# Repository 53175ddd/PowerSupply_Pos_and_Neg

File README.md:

# 正負出力電源装置

## 概要

DC 9 ~ 12V を入力すると，正負出力に変換する電源回路です  
実装する定電圧レギュレータにより出力電圧が異なります

| 正側レギュレータ（U2）の種類 | 出力電圧 | 負側レギュレータ（U3）の種類 | 出力電圧 |
|:----:|----:|:----:|----:|
| NJM7812 | 12V | NJM7912 | -12V |
| NJM7809 | 9V | NJM7909 | -9V |
| NJM7805 | 5V | NJM7905 | -5V |

## 部品表

| アノテーション | 部品定数等 | リンク |
|:----|:----|:----|
| C1 - C4 | 1uF | <https://akizukidenshi.com/catalog/g/gP-08150/> |
| C5 | 470pF | <https://akizukidenshi.com/catalog/g/gP-08130/> |
| C6 - C9 | 0.1uF | <https://akizukidenshi.com/catalog/g/gP-10147/> |
| D1 - D3 | 1N4148 | <https://akizukidenshi.com/catalog/g/gI-00941/> |
| D4 | 1JU41 | <https://akizukidenshi.com/catalog/g/gI-12820/> |
| J1 | 2.1mm DC ジャック | <https://akizukidenshi.com/catalog/g/gC-06568/> |
| J2 | 3P ターミナルブロック | <https://akizukidenshi.com/catalog/g/gP-01307/> |
| L1 | 220uH | <https://akizukidenshi.com/catalog/g/gP-13381/> |
| Q1 | TK20A60U | <https://akizukidenshi.com/catalog/g/gI-08419/> |
| Q2 | 2SA1015 | <https://akizukidenshi.com/catalog/g/gI-02612/> |
| R1 | 330Ω | <https://akizukidenshi.com/catalog/g/gR-25331/> |
| R2 | 12kΩ | <https://akizukidenshi.com/catalog/g/gR-25123/> |
| R3 | 1kΩ | <https://akizukidenshi.com/catalog/g/gR-16102/> |
| U1 | NJM2374 | <https://akizukidenshi.com/catalog/g/gI-12901/> |
| U2 | NJM7812 等 | <https://akizukidenshi.com/catalog/g/gI-00163/> |
| U3 | NJM7912 等 | <https://akizukidenshi.com/catalog/g/gI-17482/> |

## 回路図

<div align="center"></div>

## 設計イメージ図

<div align="center"></div>

## 3D イメージ図

<div align="center"></div>

# LICENSE

[CC BY-NC-SA 4.0](https://creativecommons.org/licenses/by-nc-sa/4.0/deed.ja) で公開します．ただし，営利目的で利用したい場合はその旨を `tatarariku(at)gmail.com` にてご相談ください

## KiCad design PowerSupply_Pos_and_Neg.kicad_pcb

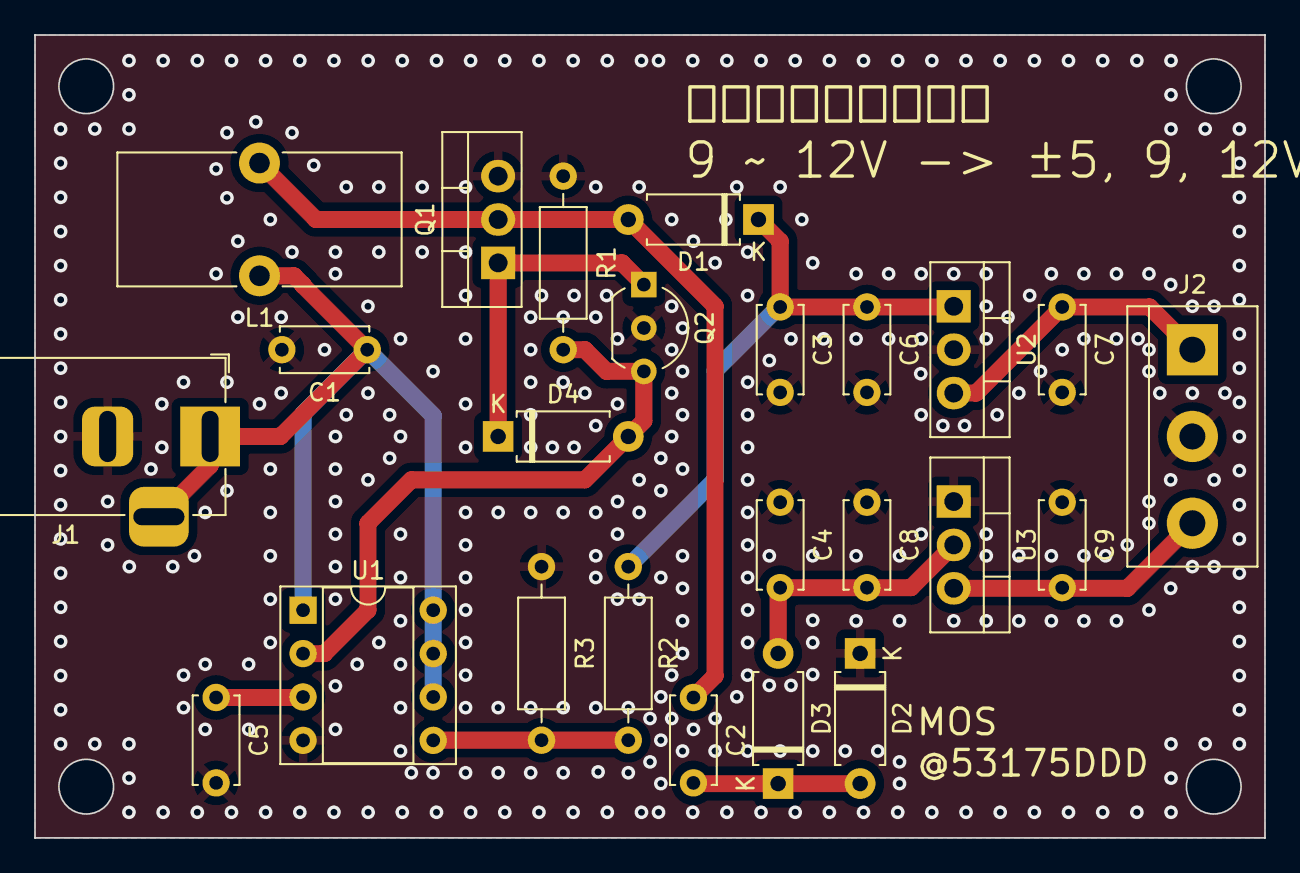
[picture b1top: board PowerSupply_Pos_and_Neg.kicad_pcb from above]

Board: 2 copper layers, 72.0 x 47.0 mm, 24 parts (0 on the bottom side), 12 nets.

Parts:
C1, C2, C3, C4: 1uF; C_Disc_D5.0mm_W2.5mm_P5.00mm
C5: 470pF; C_Disc_D5.0mm_W2.5mm_P5.00mm
C6, C7, C8, C9: 0.1uF; C_Disc_D5.0mm_W2.5mm_P5.00mm
D1, D2, D3, D4: 1N4148; D_A-405_P7.62mm_Horizontal
J1: Barrel_Jack_Switch_MountingPin; BarrelJack_Horizontal
J2: Screw_Terminal_01x03; TerminalBlock_bornier-3_P5.08mm
L1: L; L_Toroid_Vertical_L16.4mm_W7.6mm_P6.60mm_Vishay_TJ3
Q1: TK20A60U; TO-220-3_Vertical
Q2: 2SA1015; TO-92_Inline_Wide
R1: 300Ω; R_Axial_DIN0207_L6.3mm_D2.5mm_P10.16mm_Horizontal
R2: 10kΩ; R_Axial_DIN0207_L6.3mm_D2.5mm_P10.16mm_Horizontal
R3: 1kΩ; R_Axial_DIN0207_L6.3mm_D2.5mm_P10.16mm_Horizontal
U1: DIP-8_W7.62mm_Socket
U2: L7812; TO-220-3_Vertical
U3: L7912; TO-220-3_Vertical

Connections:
+12V: C1.1, J1.1, J1.3, L1.1, U1.1 (Cs), U1.6 (V+), U1.7 (Si), U1.8 (Cd)
GATE: D4.1 (K), Q1.1 (G), Q2.1 (E)
GND: C1.2, C3.2, C4.1, C5.2, C6.2, C7.2, C8.1, C9.1, D2.1 (K), J1.2, J2.2, Q1.3 (S), Q2.2 (C), R1.2, R3.2, U1.4 (GND), U2.2 (GND), U3.1 (GND)
unnamed: C2.1, D1.2 (A), L1.2, Q1.2 (D)
unnamed: C2.2, D2.2 (A), D3.1 (K)
unnamed: C7.1, J2.1, U2.3 (OUT)
unnamed: C9.2, J2.3, U3.3 (VO)
unnamed: C5.1, U1.3 (Cr)
unnamed: R2.2, R3.1, U1.5 (IN+)
VCC: C3.1, C6.1, D1.1 (K), R2.1, U2.1 (IN)
VEE: C4.2, C8.2, D3.2 (A), U3.2 (VI)
signal_GATE: D4.2 (A), Q2.3 (B), R1.1, U1.2 (Es)

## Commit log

2023-12-22 add *.png
2023-12-22 first commit as v1
2023-12-22 add bom
2023-12-26 部品変更
